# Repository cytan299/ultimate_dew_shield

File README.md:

# The Ultimate Dew Shield

by C.Y. Tan 2016

I looked at the commercially available dew shields for my 8" LX200 and
I thought that I could do better. The requirements for my dew shield
are as follows:

* I want my dew shield to be perfectly fitted on my LX200 that takes
  into account the optical rails that are mounted on both the top and
  bottom of my LX200.
* I want a temperature controller for the dew shield that
measures both the dew point as well as the ambient temperature. The
controller will use these temperature measurements to set the
internal temperature of the dew shield to a differential temperature
that is set by the user.

## Support

All the software have been successfully compiled on Mac OS X 10.10.5
(Yosemite) and 10.11.2 (El Capitan) running Arduino IDE 1.6.5. Note:
Later versions of Arduino IDE cannot compile the Arduino Pro Micro
library. See the README.md in the arduino directory for more
information.

This is unsupported software and hardware. Build at your own peril! :)

You can submit questions or bug reports using the
[issues](https://github.com/cytan299/ultimate_dew_shield/issues) tab on
the right and then click on **NEW**.

Have fun!

## Directory structure

* **arduino** The C++ code for the Arduino Pro Micro.
* **arduino_case** The case design for the controller.
* **bom** Bill of materials for 1 ultimate dew shield. 
* **eagle** Eagle schematic and board files.
* **howto** Guides for how to assemble the dew shield and the
controller.
* **controller_analysis** The analysis of the temperature control
loop.
* **writeup** A writeup of the motivation and analysis of the
  Ultimate Dew Shield.

## Other information

More information can be found in he *README.md* files in each
directory and the [wiki](https://github.com/cytan299/ultimate_dew_shield/wiki/The-Ultimate-Dew-Shield) of this project on github.

## Copyright
All the software, documentation, hardware that I have written is
copyright 2016 C.Y. Tan.

All software is released under GPLv3

All documentation is released under Creative Commons
Attribution-ShareAlike 3.0 Unported License or GNU Free
Documentation License, Version 1.3

All hardware is released under CERN Hardware Open License v1.2

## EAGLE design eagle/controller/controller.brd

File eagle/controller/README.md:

# Controller Module

The controller module is mounted on the dew shield. It monitors the
temperatures inside and outside the dew shield, and the relative
humidity.

## Copyright

The schematic and board designs are copyright 2016 C.Y. Tan and
released under the CERN Open Hardware License v1.2

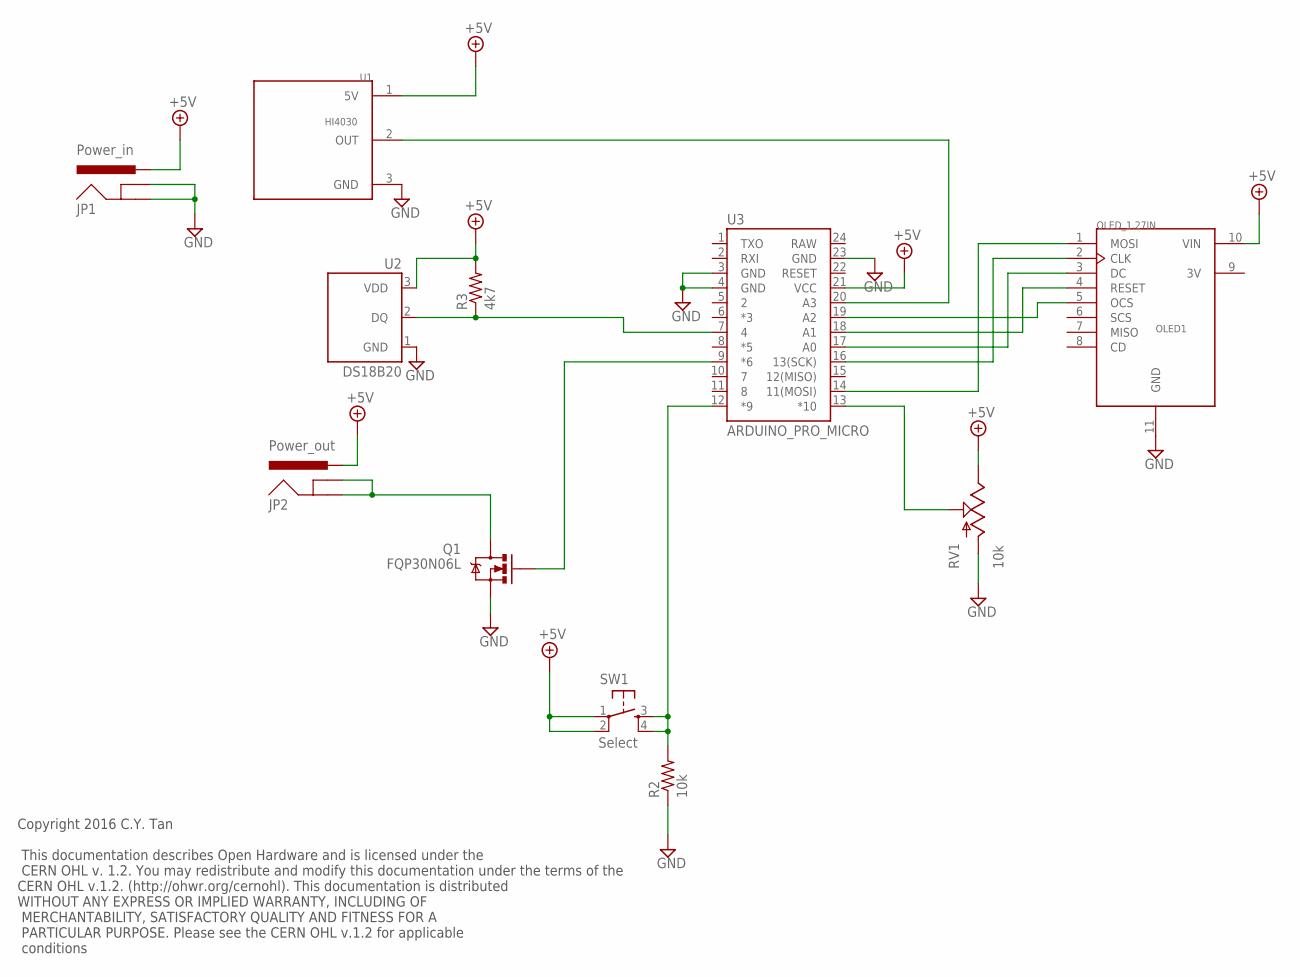
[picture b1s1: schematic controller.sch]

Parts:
JP1: Power_in; POWER_JACK_PTH
JP2: Power_out; POWER_JACK_PTH
OLED1: OLED_1.27IN; OLED_1.27INCH
Q1: FQP30N06L; TO220V
R2: 10k; AXIAL-0.3
R3: 4k7; AXIAL-0.3
RV1: 10k; ALPS_POT_KIT
SW1: Select; TAC-SWITCH-PTH
U1: HI4030; 1X03
U2: DS18B20; TO-92-AMMO
U3: ARDUINO_PRO_MICRO

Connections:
3V: OLED1.9 (3V)
+5V: JP1.PWR, JP2.PWR, OLED1.10 (VIN), R3.P$2 (2), RV1.P$1 (E), SW1.1, SW1.2, U1.1 (5V), U2.3 (VDD), U3.21 (VCC)
GND: JP1.GND, JP1.GNDBREAK, OLED1.11 (GND), Q1.3 (S), R2.P$1 (1), RV1.P$3 (A), U1.3 (GND), U2.1 (GND), U3.3 (GND), U3.4 (GND), U3.23 (GND)
unnamed: OLED1.1 (MOSI), U3.14 (11(MOSI))
unnamed: OLED1.2 (CLK), U3.16 (13(SCK))
unnamed: OLED1.3 (DC), U3.17 (A0)
unnamed: JP2.GND, JP2.GNDBREAK, Q1.2 (D)
unnamed: OLED1.4 (RESET), U3.18 (A1)
unnamed: OLED1.5 (OCS), U3.19 (A2)
unnamed: Q1.1 (G), U3.9 (*6)
unnamed: RV1.P$2 (S), U3.13 (*10)
unnamed: R2.P$2 (2), SW1.3, SW1.4, U3.12 (*9)
unnamed: U1.2 (OUT), U3.20 (A3)
unnamed: R3.P$1 (1), U2.2 (DQ), U3.7 (4)

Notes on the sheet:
Copyright 2016 C.Y. Tan This documentation describes Open Hardware and is licensed under the CERN OHL v. 1.2. You may redistribute and modify this documentation under the terms of the CERN OHL v.1.2. (http://ohwr.org/cernohl). This documentation is distributed WITHOUT ANY EXPRESS OR IMPLIED WARRANT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

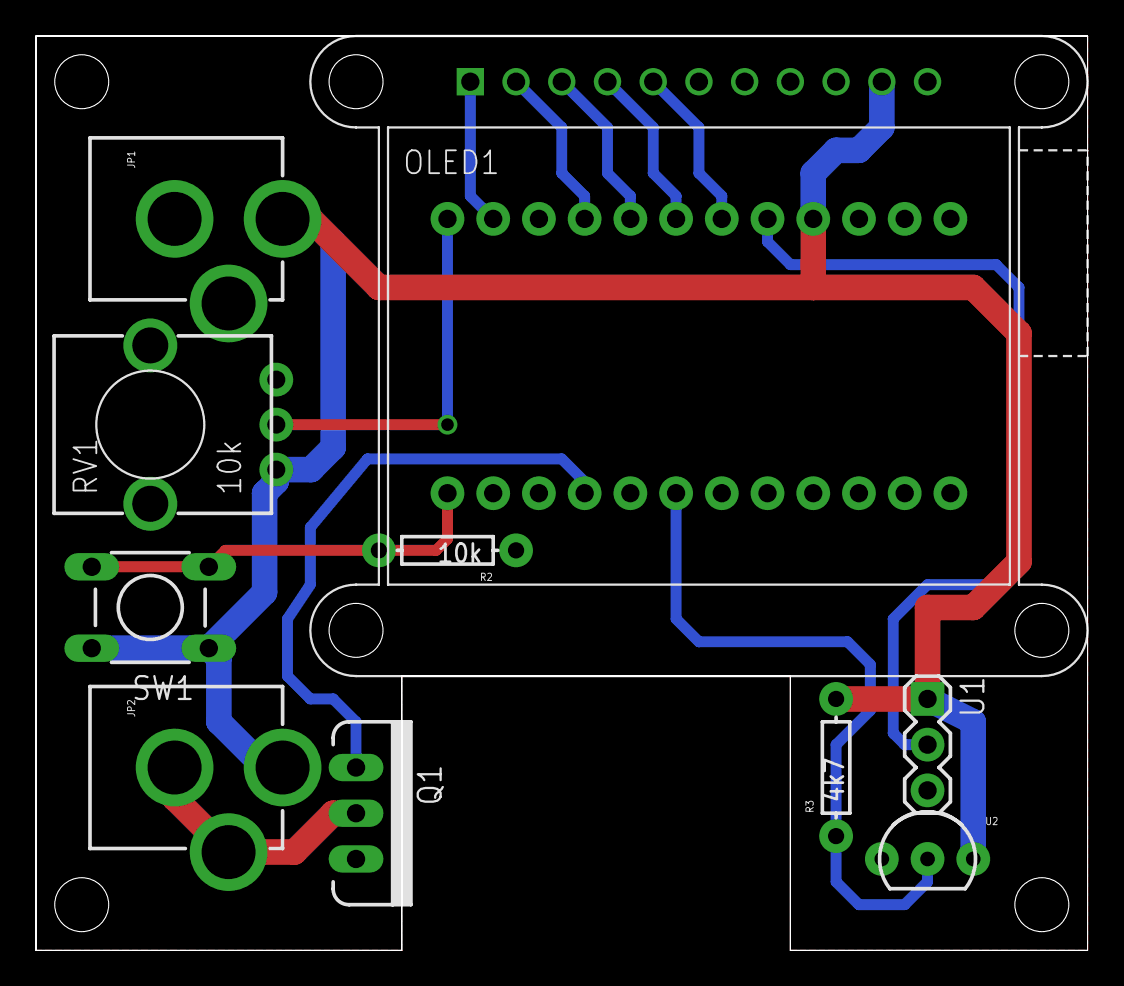
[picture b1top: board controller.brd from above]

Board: 2 copper layers, 58.4 x 50.8 mm, 11 parts (1 on the bottom side), 13 nets.

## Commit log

2016-01-19 Initial commit. Still missing are: (a) in howto subdirectory: controller.pdf (b) writeup on how the controller works.
2016-01-20 bom: Updated bill of materials. eagle: Updated controller.sch and controller.pdf. howto: Added controller.pdf.
2016-01-20 wiki_pics: Added track_results1.png
2016-01-20 arduino: Updated controller code to send measurement data out whenever a USB cable is connected
2016-01-20 README.md: Fixed bad link to wiki
2016-01-20 wiki_pics: Added cabling.png and displayB.png
2016-01-20 arduino: Updated README.md and controller.ino
2016-01-21 howto: Added slide about fuse in controller.pdf
2016-01-22 arduino: Push button now toggles between full info and min info displays.
2016-01-22 wiki_pics: Added and updated photos.
2016-01-22 howto: controller.pdf: removed statement that push button is not used.
2016-01-22 Added controller_analysis directory
2016-01-25 arduino: Updated synopsis
2016-01-30 controller_analysis: Added controller_analysis.pdf. wiki_pics: Added installed.png
2016-04-06 Added writeup of the ultimate dew shield
2016-04-06 README.md: Updated info about the writeup directory

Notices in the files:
parts and their libraries:
SparkFun-Boards: Licensing: Creative Commons ShareAlike 4.0 International - https://creativecommons.org/licenses/by-sa/4.0
